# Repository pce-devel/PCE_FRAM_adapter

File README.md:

# FRAM converter boards

The PC Engine series of systems has a different game-save storage system than most people
these days have gotten used to.  It used a 2KB static RAM.  This wasn't in the cartridges
themselves; initially, it was sold as pat of an add-on to the system: The Tennokoe 2,
"Voice from Heaven".  In later systems like the Duo series, it would be integrated into
the system unit, yet still be limited to 2KB static RAM.

You're probably thinking, "Static RAM is volatile - it loses its contents when the power
is shut off", and you'd be right.  There really weren't any non-volatiole options at the
time.  Instead, they used batteries or large capacitors to apply continuous power to the
memory, so that it would not lose its contents.  In the case of the Tennokoe 2, 2 "AA"
cells were used; in the case of the Duo, a large capacitor was used.

I have lost a few game saves on my Duo because I failed to turn the system on for a period
of time long enough to lose its contents... probably about 1 to 2 weeks.

Because of this, I was inspired to replace the SRAM with modern FeRAM to make it
non-volatile.  But the Duo is a tighter-packed PC board with surface-mount chips, so I felt it
was easier to first test the idea on the Tennokoe 2, which uses a DIP SRAM chip.

I have followed up with a design for a flex PCB to use with surface-mount chips in order to
be suitable for my Duo, and it also works well.

I chose to use the Cypress FM16W08 chip, which can handle 5V, has timing which is
equal to or better than the SRAM it is replacing, and has a similar pinout.  But I still
needed to make adapter boards (which is what this repository is all about).

As the FeRAM is rated for 100 trillion read/write cycles, there is no
concern about lifetime under the usage in this application.

I designed the boards using the free version of EAGLE (2-layer, less than 100mm
on both X- and Y-axes).  The gerbers are included in this repository, in case you
want to get your own set made.

## Assembly/installation instructions for the FRAM-DIP board for the Tennokoe 2:

https://github.com/dshadoff/PCE_FRAM_adapter/blob/master/FRAM-DIP-assembly.md

## Assembly/installation instructions for the FRAM-SOIC board for the Duo and other machines:

https://github.com/dshadoff/PCE_FRAM_adapter/blob/master/FRAM-SOIC-assembly.md

## UPDATE: A new board for use with the PCE Shuttle Backup Memory

The Shuttle's board was designed using KiCAD. While this board is separate and distinct from
the board for the Tennokoe 2, the installation instructions are similar (sorry, but I don't
have pictures)

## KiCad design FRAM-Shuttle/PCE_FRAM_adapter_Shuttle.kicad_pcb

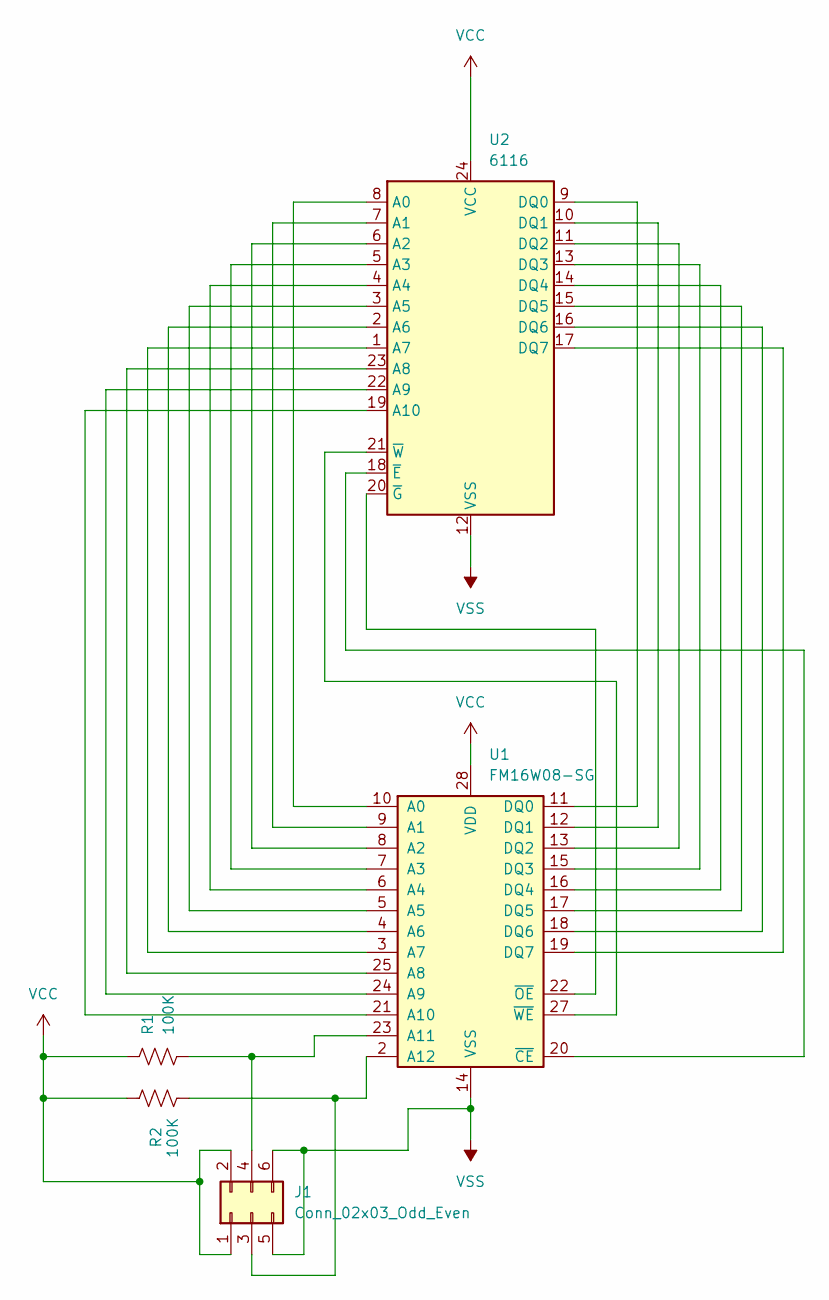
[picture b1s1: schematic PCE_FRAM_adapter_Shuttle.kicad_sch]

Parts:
J1: Conn_02x03_Odd_Even; PinHeader_2x03_P2.00mm_Vertical
R1, R2: 100K; R_0805_2012Metric_Pad1.20x1.40mm_HandSolder
U1: FM16W08-SG; SOIC-28W_7.5x17.9mm_P1.27mm
U2: 6116; DIP-24_18.0mmx34.29mm_W15.24mm

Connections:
unnamed: J1.3, R2.2, U1.2 (A12)
unnamed: J1.4, R1.2, U1.23 (A11)
unnamed: U1.10 (A0), U2.8 (A0)
unnamed: U1.9 (A1), U2.7 (A1)
unnamed: U1.8 (A2), U2.6 (A2)
unnamed: U1.7 (A3), U2.5 (A3)
unnamed: U1.6 (A4), U2.4 (A4)
unnamed: U1.5 (A5), U2.3 (A5)
unnamed: U1.4 (A6), U2.2 (A6)
unnamed: U1.3 (A7), U2.1 (A7)
unnamed: U1.25 (A8), U2.23 (A8)
unnamed: U1.24 (A9), U2.22 (A9)
unnamed: U1.21 (A10), U2.19 (A10)
unnamed: U1.11 (DQ0), U2.9 (DQ0)
unnamed: U1.12 (DQ1), U2.10 (DQ1)
unnamed: U1.13 (DQ2), U2.11 (DQ2)
unnamed: U1.15 (DQ3), U2.13 (DQ3)
unnamed: U1.16 (DQ4), U2.14 (DQ4)
unnamed: U1.17 (DQ5), U2.15 (DQ5)
unnamed: U1.18 (DQ6), U2.16 (DQ6)
unnamed: U1.19 (DQ7), U2.17 (DQ7)
unnamed: U1.20 (~CE), U2.18 (~E)
unnamed: U1.22 (~OE), U2.20 (~G)
unnamed: U1.27 (~WE), U2.21 (~W)
VCC: J1.1, J1.2, R1.1, R2.1, U1.28 (VDD), U2.24 (VCC)
VSS: J1.5, J1.6, U1.14 (VSS), U2.12 (VSS)

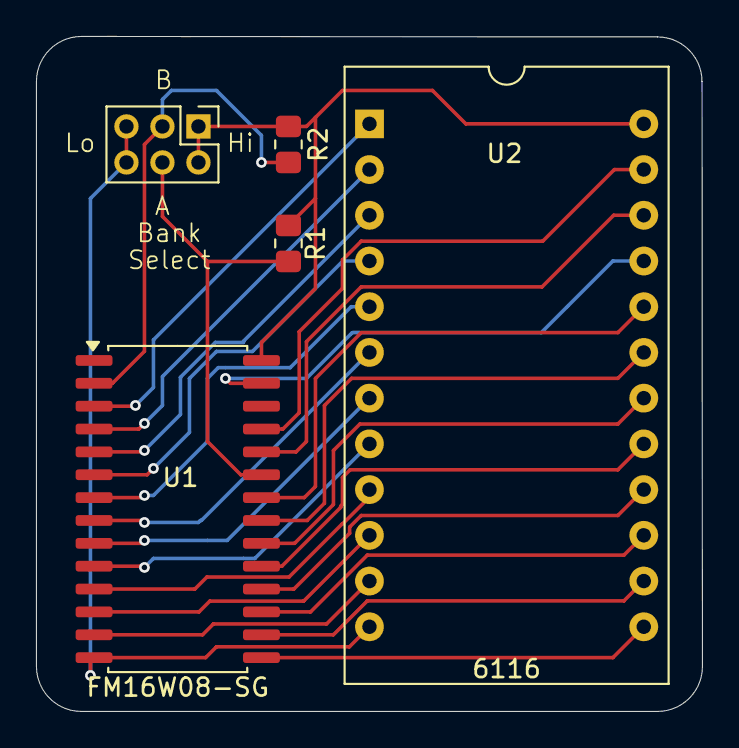
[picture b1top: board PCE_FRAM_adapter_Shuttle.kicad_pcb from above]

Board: 2 copper layers, 37.0 x 37.5 mm, 5 parts (0 on the bottom side), 26 nets.

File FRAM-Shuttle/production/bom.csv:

Designator,Footprint,Quantity,Value,LCSC Part #
J1,PinHeader_2x03_P2.00mm_Vertical,1,Conn_02x03_Odd_Even,
"R1, R2",0805,2,100K,
U1,SOIC-28W_7.5x17.9mm_P1.27mm,1,FM16W08-SG,
U2,DIP-24_18.0mmx34.29mm_W15.24mm,1,6116,

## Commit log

2020-07-02 Initial commit
    Initial commit; board to replace DIP SRAM in Tennokoe 2 unit
2020-07-02 Fix typo
2020-07-08 Update Installation documents
2020-07-08 Edits
2020-07-08 More edits
2020-07-11 Add surface-mount version
    A surface-mount version, to support the Duo machine, is added
2020-07-11 Add SOIC board
2024-04-01 Create a new revision of the FRAM SOP board
2026-01-11 Add FRAM adapter for PCE Shuttle Backup Memory Unti
